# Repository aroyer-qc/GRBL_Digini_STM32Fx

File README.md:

# GRBL_Digini_STM32Fx

Grbl is a no-compromise, high performance, low cost alternative to parallel-port-based motion control for CNC milling. This version will run on a stm32f7-discovery and later on other STM32 family.
The controller is written in highly optimized C utilizing every clever feature of the STM32F7 to achieve precise timing and asynchronous operation. It will be able to maintain more than the original 30kHz from Arduino of stable, jitter free control pulses.

Digini is a HAL and GUI library written in embedded C++. It is highly optimized and is also a highly configurable graphic library. GUI is based on Widget/Service concept. What this mean is, the application like GRBL run on his own loop, and is not aware the GUI even exist. the GUI on his side is running multiple task to display graphic page. Those page are a chain list of widget, and those widget are configured with information about position, graphic to use, service to call to display the proper information and link to other page. all information is processed via variables and/or call to users functions.

  ## Note(s):
  
>   * GRBL is a great application for me to develop the graphic DIGINI platform.
>   * Widget are easy to add in Digini.
    
  ## Feature:

>   * Code is C++ (following embedded rules found on IAR C++ document Inefficiencies of C++: Fact or Fiction?).
>   * Run on nOS from Jim Tremblay. See [RTOS for microcontrollers](https://github.com/jimtremblay/nOS)
>   * Digini graphics run parallel and independant of the main application, all graphics are handles via service.
>   * Data are display by hooking to variables and/or by calling function(s), input are also done via variables and/or function(s). no graphic code exist in application.
>   * Control over the application can be done via state machine and/or message at the discretion of the application user.
>   * Skin data is loaded from SD card via a skin file (.skn). to build a skin file you can used my application [GUI_Builder](https://github.com/aroyer-qc/GUI_Builder)

  ## Widget list so far:
  
>    * Background widget to display background layer.
>    * Basic box.
>    * Basic button with text (no graphic).
>    * Basic rectangle.
>    * Button with text, icon and support for multiple graphic so button can have different state. ( EX. normal, pressed, gray out)
>    * Exchange is a non grahical special widget to exchange data between graphic page.
>    * Gif to display gif as animation.
>    * Icon support for multiple graphic to display different state.
>    * Label to display static/formatted label. also support for different language.
>    * Label list, like label but with a list different label according to state.
>    * Meter, WIP.
>    * Panel, can add touch zone with graphics under other widget.
>    * Progress bar.
>    * Spectrum analyser display (Use data from application, no processing).
>    * Terminal basic terminal screen.
>    * Virtual is a non grahical special widget to decide whart page to display according to application setting.
>    * Virtual windows (WIP).
  
  ## Standard service provided in library
  
>    * SERV_ID_BACK    Service to copy background to background layer.
>    * SERV_ID_BDEF    Service to handle button used only to jump to other page link. Ex. Setting, Back, Ok, etc...
>    * SERV_ID_DATE    Service to return the date of the system into a formatted string.
>    * SERV_ID_DAYS    Service to return the days of the system into a formatted string.
>    * SERV_ID_INPT    Service to input data via a generic page in decimal or hexa.
>    * SERV_ID_INPS    Service to input string via a generic page. (WIP).
>    * SERV_ID_NONE    Service to return default state
>    * SERV_ID_RFSH    Service to display static widget
>    * SERV_ID_SKLD    Service to return percentage of the skin loading progression
>    * SERV_ID_TIME    Service to return the timeof the system into a formatted string (can handle all format defined by user).
>    * SERV_ID_XCHG    Service to exchange data via structure between page. (title, min, max, value, edit type)

  ## Required Module:
  
>    *   Digini                        (Branch Develop)
>    *   module_FatFs                  (Branch main)
>    *   module_jpg                    (Branch main)
>    *   lwip                          (Branch STABLE_2_1_x)
>    *   module_picopng                (Branch main)
>    *   module_STM32F7xx              (Branch main)
>    *   nOS                           (Branch master)

  ## Known issues
  
>    * Stepper not yet working, I need to test the STM32 timer and integrate them into the GRBL code.
>    * Spindle not yet working, PWM need to be tested and integrated.
>    * Cross exchange GRBL <-> GUI to be done..
>    * A lot of graphic page to fix/complete.
>    * Add sound capability to get some aptic feedback.

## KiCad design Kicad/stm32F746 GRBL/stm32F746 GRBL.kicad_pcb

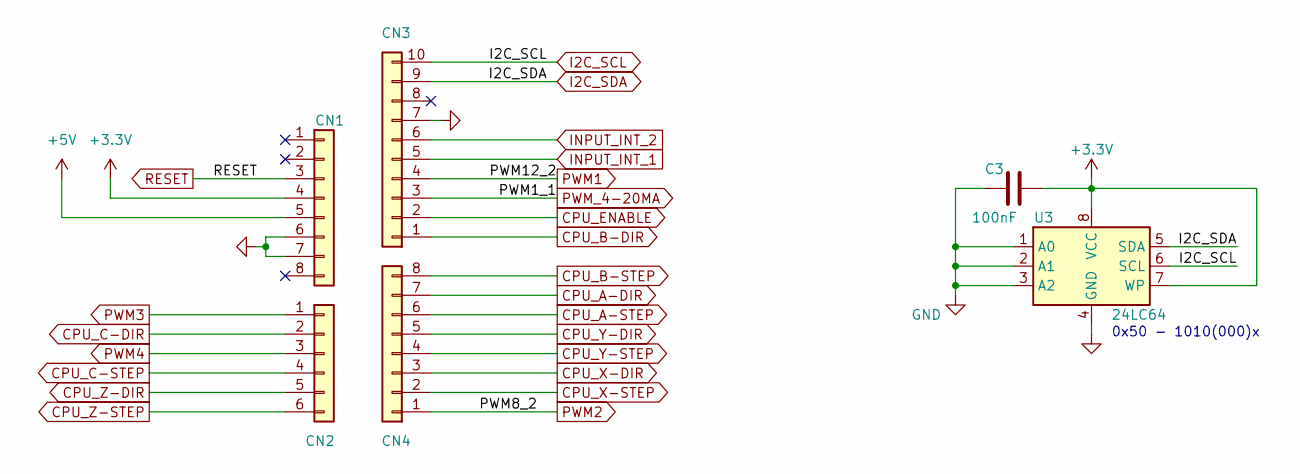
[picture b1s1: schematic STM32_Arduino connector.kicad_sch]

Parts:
C3: 100nF; C_0805_2012Metric
CN1, CN4: PinHeader_1x08_P2.54mm_Vertical
CN2: PinHeader_1x06_P2.54mm_Vertical
CN3: PinHeader_1x10_P2.54mm_Vertical
U3: 24LC64; SOIC-8_3.9x4.9mm_P1.27mm

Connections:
+3.3V: C3.2, CN1.4, U3.7 (WP), U3.8 (VCC)
+5V: CN1.5
CPU_A-DIR: CN4.7; also elsewhere on the board
CPU_A-STEP: CN4.6; also elsewhere on the board
CPU_B-DIR: CN3.1; also elsewhere on the board
CPU_B-STEP: CN4.8; also elsewhere on the board
CPU_C-DIR: CN2.2; also elsewhere on the board
CPU_C-STEP: CN2.4; also elsewhere on the board
CPU_ENABLE: CN3.2; also elsewhere on the board
CPU_X-DIR: CN4.3; also elsewhere on the board
CPU_X-STEP: CN4.2; also elsewhere on the board
CPU_Y-DIR: CN4.5; also elsewhere on the board
CPU_Y-STEP: CN4.4; also elsewhere on the board
CPU_Z-DIR: CN2.5; also elsewhere on the board
CPU_Z-STEP: CN2.6; also elsewhere on the board
GND: C3.1, CN1.6, CN1.7, CN3.7, U3.1 (A0), U3.2 (A1), U3.3 (A2), U3.4 (GND); also elsewhere on the board
I2C_SCL: CN3.10, U3.6 (SCL); also elsewhere on the board
I2C_SDA: CN3.9, U3.5 (SDA); also elsewhere on the board
INPUT_INT_1: CN3.5; also elsewhere on the board
INPUT_INT_2: CN3.6; also elsewhere on the board
PWM1: CN3.4; also elsewhere on the board
PWM2: CN4.1; also elsewhere on the board
PWM3: CN2.1; also elsewhere on the board
PWM4: CN2.3; also elsewhere on the board
PWM_4-20MA: CN3.3; also elsewhere on the board
RESET: CN1.3; also elsewhere on the board

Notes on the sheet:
0x50 - 1010(000)x

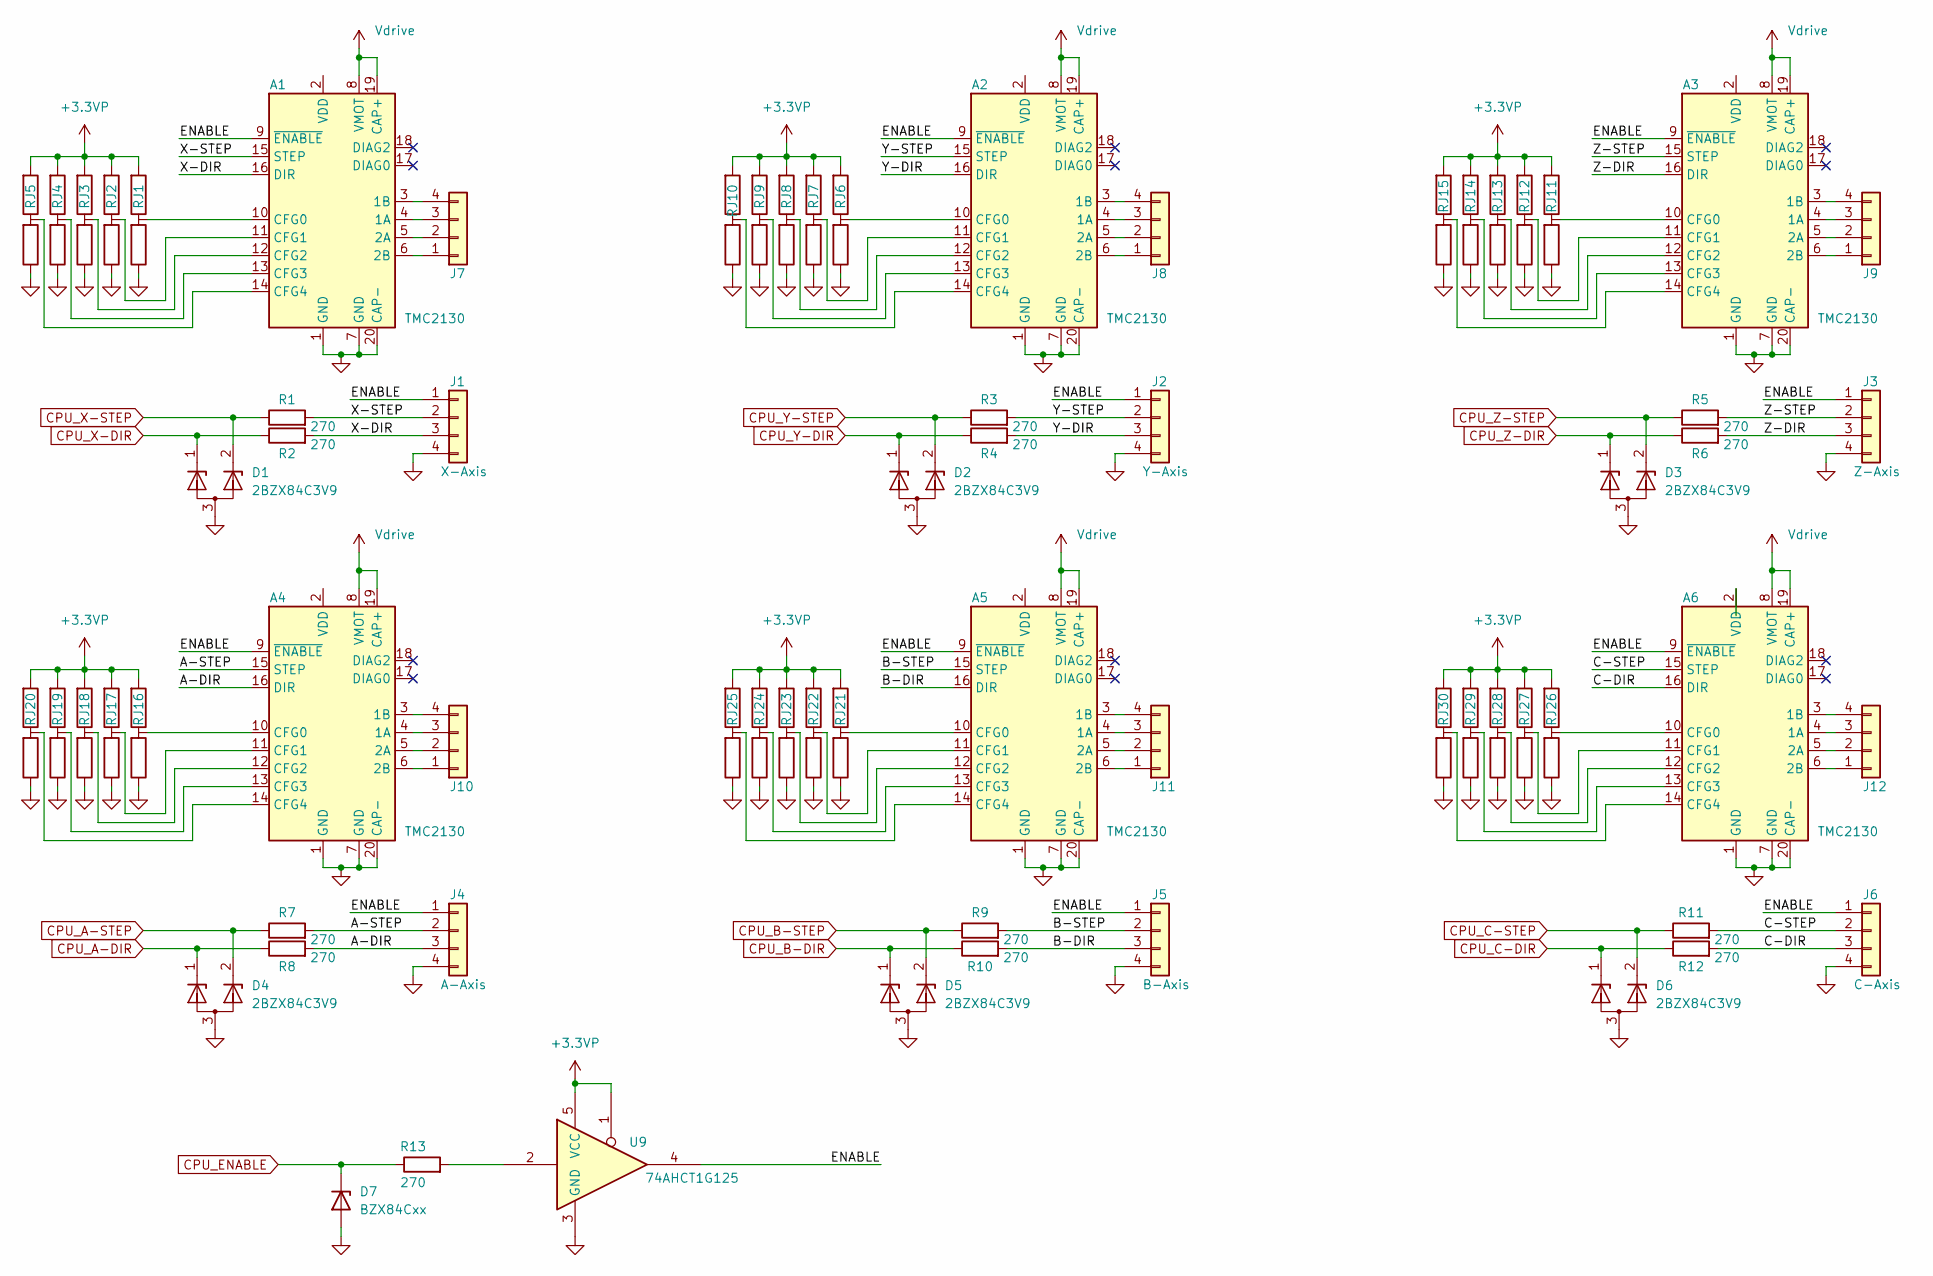
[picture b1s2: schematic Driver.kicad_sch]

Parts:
A1, A2, A3, A4, A5, A6: TMC2130_Breakout_TMC2130; TMC2130_Breakout-16_15.2x20.3mm
D1, D2, D3, D4, D5, D6: 2BZX84C3V9; SOT-23
D7: BZX84Cxx; SOT-23
J1: X-Axis; JST_XH_B4B-XH-A_1x04_P2.50mm_Vertical
J2: Y-Axis; JST_XH_B4B-XH-A_1x04_P2.50mm_Vertical
J3: Z-Axis; JST_XH_B4B-XH-A_1x04_P2.50mm_Vertical
J4: A-Axis; JST_XH_B4B-XH-A_1x04_P2.50mm_Vertical
J5: B-Axis; JST_XH_B4B-XH-A_1x04_P2.50mm_Vertical
J6: C-Axis; JST_XH_B4B-XH-A_1x04_P2.50mm_Vertical
J7, J8, J9, J10, J11, J12: Conn_01x04; JST_XH_B4B-XH-A_1x04_P2.50mm_Vertical
R1, R2, R3, R4, R5, R6, R7, R8, R9, R10, R11, R12, R13: 270; R_0805_2012Metric
RJ1, RJ2, RJ3, RJ4, RJ5, RJ6, RJ7, RJ8, RJ9, RJ10, RJ11, RJ12, RJ13, RJ14, RJ15, RJ16, RJ17, RJ18, RJ19, RJ20, RJ21, RJ22, RJ23, RJ24, RJ25, RJ26, RJ27, RJ28, RJ29, RJ30: 0R; RJ_3 pads_0805_2012Metric
U9: 74AHCT1G125; SOT-353_SC-70-5

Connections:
+3.3VP: RJ1.1, RJ2.1, RJ3.1, RJ4.1, RJ5.1, RJ6.1, RJ7.1, RJ8.1, RJ9.1, RJ10.1, RJ11.1, RJ12.1, RJ13.1, RJ14.1, RJ15.1, RJ16.1, RJ17.1, RJ18.1, RJ19.1, RJ20.1, RJ21.1, RJ22.1, RJ23.1, RJ24.1, RJ25.1, RJ26.1, RJ27.1, RJ28.1, RJ29.1, RJ30.1, U9.1, U9.5 (VCC); also elsewhere on the board
/Driver/A-DIR: A4.16 (DIR), J4.3, R8.2
/Driver/A-STEP: A4.15 (STEP), J4.2, R7.2
/Driver/B-DIR: A5.16 (DIR), J5.3, R10.2
/Driver/B-STEP: A5.15 (STEP), J5.2, R9.2
/Driver/C-DIR: A6.16 (DIR), J6.3, R12.2
/Driver/C-STEP: A6.15 (STEP), J6.2, R11.2
/Driver/ENABLE: A1.9 (~ENABLE), A2.9 (~ENABLE), A3.9 (~ENABLE), A4.9 (~ENABLE), A5.9 (~ENABLE), A6.9 (~ENABLE), J1.1, J2.1, J3.1, J4.1, J5.1, J6.1, U9.4
/Driver/X-DIR: A1.16 (DIR), J1.3, R2.2
/Driver/X-STEP: A1.15 (STEP), J1.2, R1.2
/Driver/Y-DIR: A2.16 (DIR), J2.3, R4.2
/Driver/Y-STEP: A2.15 (STEP), J2.2, R3.2
/Driver/Z-DIR: A3.16 (DIR), J3.3, R6.2
/Driver/Z-STEP: A3.15 (STEP), J3.2, R5.2
CPU_A-DIR: D4.1 (K), R8.1; also elsewhere on the board
CPU_A-STEP: D4.2 (K), R7.1; also elsewhere on the board
CPU_B-DIR: D5.1 (K), R10.1; also elsewhere on the board
CPU_B-STEP: D5.2 (K), R9.1; also elsewhere on the board
CPU_C-DIR: D6.1 (K), R12.1; also elsewhere on the board
CPU_C-STEP: D6.2 (K), R11.1; also elsewhere on the board
CPU_ENABLE: D7.3 (K), R13.1; also elsewhere on the board
CPU_X-DIR: D1.1 (K), R2.1; also elsewhere on the board
CPU_X-STEP: D1.2 (K), R1.1; also elsewhere on the board
CPU_Y-DIR: D2.1 (K), R4.1; also elsewhere on the board
CPU_Y-STEP: D2.2 (K), R3.1; also elsewhere on the board
CPU_Z-DIR: D3.1 (K), R6.1; also elsewhere on the board
CPU_Z-STEP: D3.2 (K), R5.1; also elsewhere on the board
GND: A1.1 (GND), A1.7 (GND), A1.20 (CAP-), A2.1 (GND), A2.7 (GND), A2.20 (CAP-), A3.1 (GND), A3.7 (GND), A3.20 (CAP-), A4.1 (GND), A4.7 (GND), A4.20 (CAP-), A5.1 (GND), A5.7 (GND), A5.20 (CAP-), A6.1 (GND), A6.7 (GND), A6.20 (CAP-), D1.3 (A), D2.3 (A), D3.3 (A), D4.3 (A), D5.3 (A), D6.3 (A), D7.1 (A), J1.4, J2.4, J3.4, J4.4, J5.4, J6.4, RJ1.3, RJ2.3, RJ3.3, RJ4.3, RJ5.3, RJ6.3, RJ7.3, RJ8.3, RJ9.3, RJ10.3, RJ11.3, RJ12.3, RJ13.3, RJ14.3, RJ15.3, RJ16.3, RJ17.3, RJ18.3, RJ19.3, RJ20.3, RJ21.3, RJ22.3, RJ23.3, RJ24.3, RJ25.3, RJ26.3, RJ27.3, RJ28.3, RJ29.3, RJ30.3, U9.3 (GND); also elsewhere on the board
unnamed: A1.4 (1A), J7.3
unnamed: A1.3 (1B), J7.4
unnamed: A1.5 (2A), J7.2
unnamed: A1.6 (2B), J7.1
unnamed: A1.10 (CFG0), RJ1.2
unnamed: A1.11 (CFG1), RJ2.2
unnamed: A1.12 (CFG2), RJ3.2
unnamed: A1.13 (CFG3), RJ4.2
unnamed: A1.14 (CFG4), RJ5.2
unnamed: A2.4 (1A), J8.3
unnamed: A2.3 (1B), J8.4
unnamed: A2.5 (2A), J8.2
unnamed: A2.6 (2B), J8.1
unnamed: A2.10 (CFG0), RJ6.2
unnamed: A2.11 (CFG1), RJ7.2
unnamed: A2.12 (CFG2), RJ8.2
unnamed: A2.13 (CFG3), RJ9.2
unnamed: A2.14 (CFG4), RJ10.2
unnamed: A3.4 (1A), J9.3
unnamed: A3.3 (1B), J9.4
unnamed: A3.5 (2A), J9.2
unnamed: A3.6 (2B), J9.1
unnamed: A3.10 (CFG0), RJ11.2
unnamed: A3.11 (CFG1), RJ12.2
unnamed: A3.12 (CFG2), RJ13.2
unnamed: A3.13 (CFG3), RJ14.2
unnamed: A3.14 (CFG4), RJ15.2
unnamed: A4.4 (1A), J10.3
unnamed: A4.3 (1B), J10.4
unnamed: A4.5 (2A), J10.2
unnamed: A4.6 (2B), J10.1
unnamed: A4.10 (CFG0), RJ16.2
unnamed: A4.11 (CFG1), RJ17.2
unnamed: A4.12 (CFG2), RJ18.2
unnamed: A4.13 (CFG3), RJ19.2
unnamed: A4.14 (CFG4), RJ20.2
unnamed: A5.4 (1A), J11.3
unnamed: A5.3 (1B), J11.4
unnamed: A5.5 (2A), J11.2
unnamed: A5.6 (2B), J11.1
unnamed: A5.10 (CFG0), RJ21.2
unnamed: A5.11 (CFG1), RJ22.2
unnamed: A5.12 (CFG2), RJ23.2
unnamed: A5.13 (CFG3), RJ24.2
unnamed: A5.14 (CFG4), RJ25.2
unnamed: A6.4 (1A), J12.3
unnamed: A6.3 (1B), J12.4
unnamed: A6.5 (2A), J12.2
unnamed: A6.6 (2B), J12.1
unnamed: A6.10 (CFG0), RJ26.2
unnamed: A6.11 (CFG1), RJ27.2
unnamed: A6.12 (CFG2), RJ28.2
unnamed: A6.13 (CFG3), RJ29.2
unnamed: A6.14 (CFG4), RJ30.2
unnamed: R13.2, U9.2
Vdrive: A1.8 (VMOT), A1.19 (CAP+), A2.8 (VMOT), A2.19 (CAP+), A3.8 (VMOT), A3.19 (CAP+), A4.8 (VMOT), A4.19 (CAP+), A5.8 (VMOT), A5.19 (CAP+), A6.8 (VMOT), A6.19 (CAP+); also elsewhere on the board

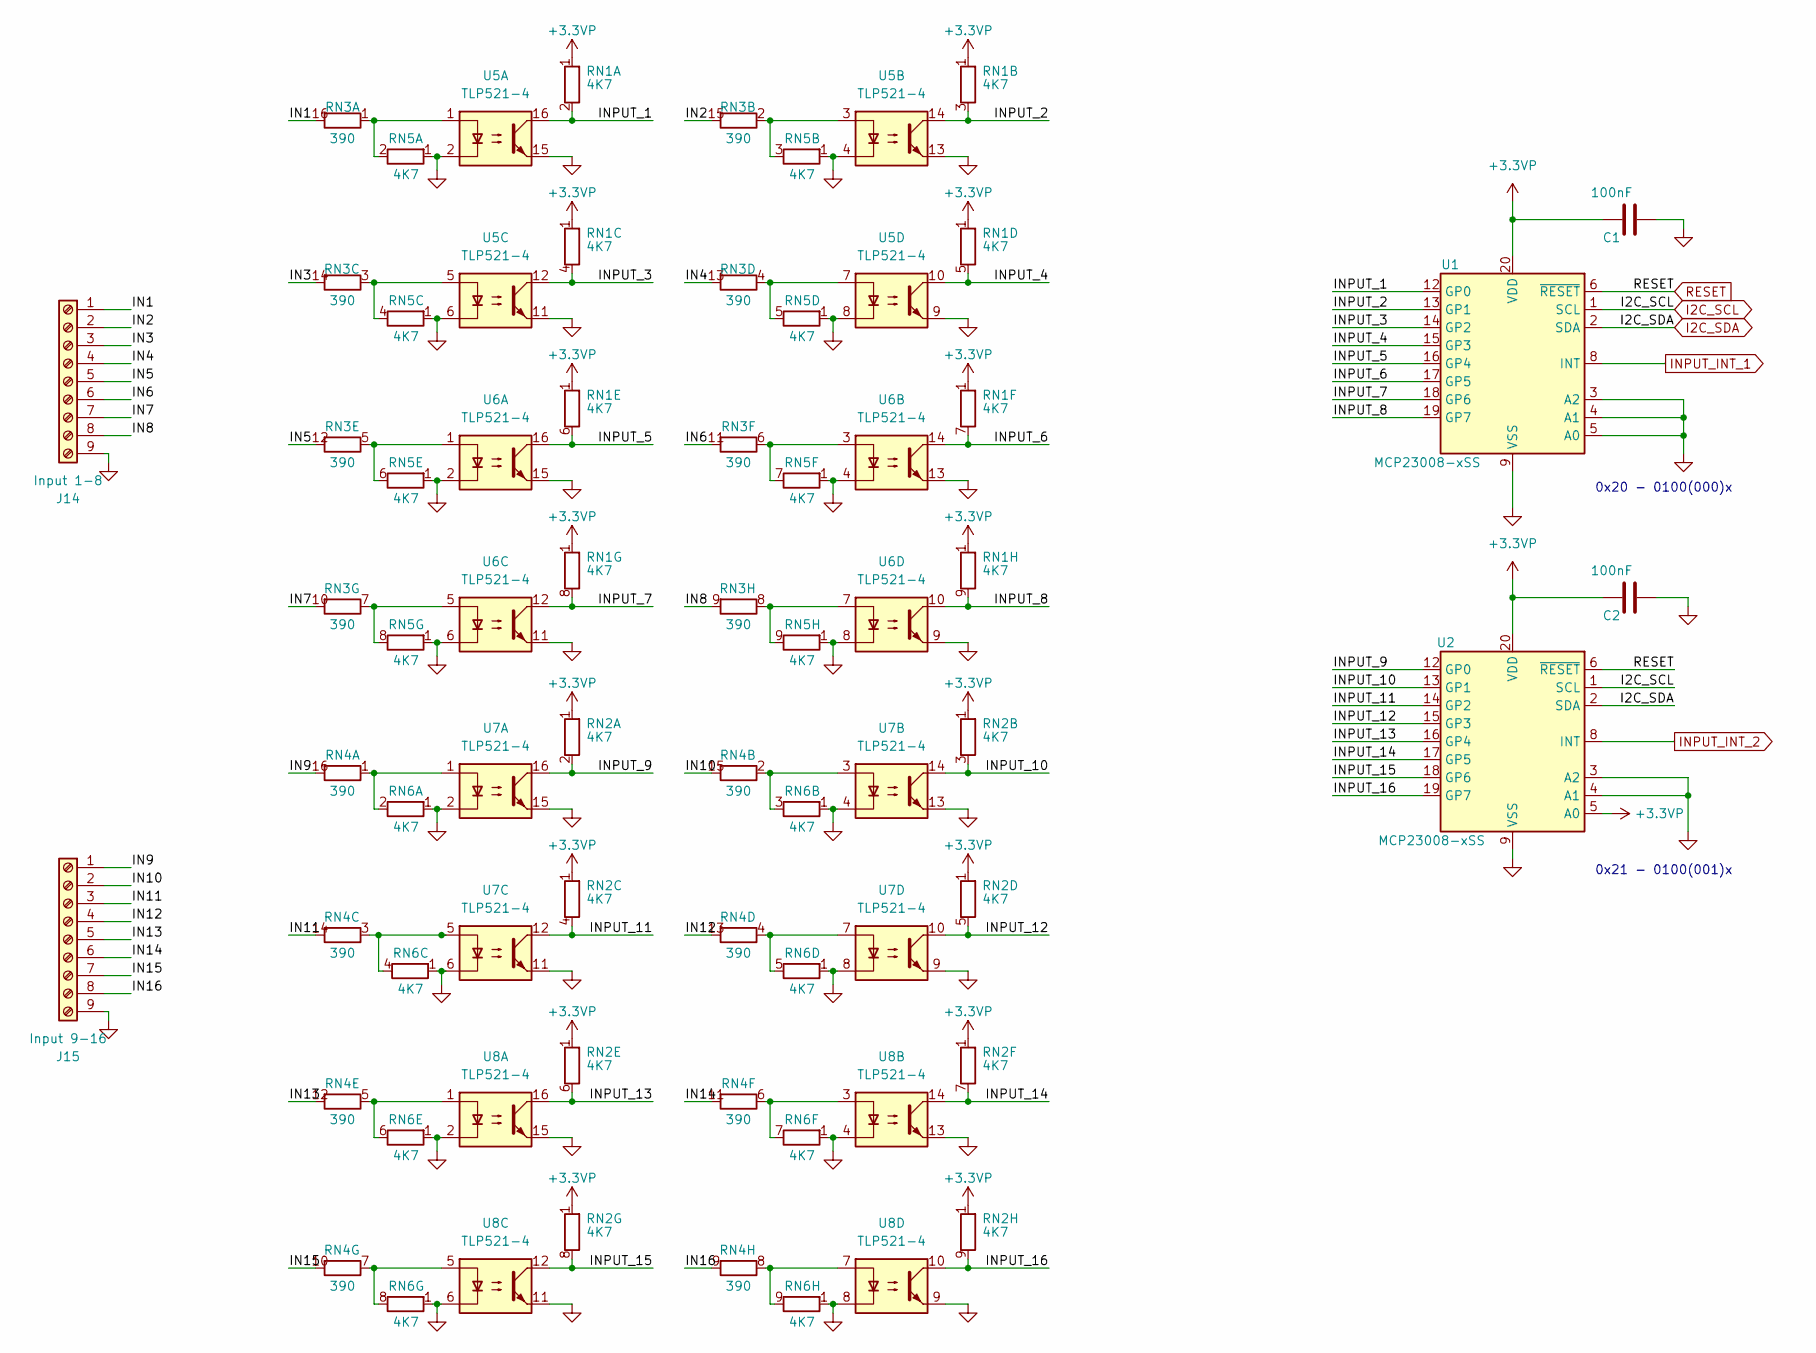
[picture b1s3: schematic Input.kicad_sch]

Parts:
C1, C2: 100nF; C_0805_2012Metric
J14: Input 1-8; TerminalBlock_TE_282834-9_1x09_P2.54mm_Horizontal
J15: Input 9-16; TerminalBlock_TE_282834-9_1x09_P2.54mm_Horizontal
RN1, RN2, RN5, RN6: 4K7; R_Array_SIP9
RN3, RN4: 390; SOIC-16_4.55x10.3mm_P1.27mm; Digikey 4816P-1-391LF
U1, U2: MCP23008-xSS; SSOP-20_5.3x7.2mm_P0.65mm
U5, U6, U7, U8: TLP521-4; SOIC-16_4.55x10.3mm_P1.27mm

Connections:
+3.3VP: C1.1, C2.1, RN1.1 (R1), RN2.1 (R1), U1.20 (VDD), U2.5 (A0), U2.20 (VDD); also elsewhere on the board
/Input/IN1: J14.1, RN3.16 (R1.2)
/Input/IN2: J14.2, RN3.15 (R2.2)
/Input/IN3: J14.3, RN3.14 (R3.2)
/Input/IN4: J14.4, RN3.13 (R4.2)
/Input/IN5: J14.5, RN3.12 (R5.2)
/Input/IN6: J14.6, RN3.11 (R6.2)
/Input/IN7: J14.7, RN3.10 (R7.2)
/Input/IN8: J14.8, RN3.9 (R8.2)
/Input/IN9: J15.1, RN4.16 (R1.2)
/Input/IN10: J15.2, RN4.15 (R2.2)
/Input/IN11: J15.3, RN4.14 (R3.2)
/Input/IN12: J15.4, RN4.13 (R4.2)
/Input/IN13: J15.5, RN4.12 (R5.2)
/Input/IN14: J15.6, RN4.11 (R6.2)
/Input/IN15: J15.7, RN4.10 (R7.2)
/Input/IN16: J15.8, RN4.9 (R8.2)
/Input/INPUT_1: RN1.2 (R1.2), U1.12 (GP0), U5.16
/Input/INPUT_2: RN1.3 (R2.2), U1.13 (GP1), U5.14
/Input/INPUT_3: RN1.4 (R3.2), U1.14 (GP2), U5.12
/Input/INPUT_4: RN1.5 (R4.2), U1.15 (GP3), U5.10
/Input/INPUT_5: RN1.6 (R5.2), U1.16 (GP4), U6.16
/Input/INPUT_6: RN1.7 (R6.2), U1.17 (GP5), U6.14
/Input/INPUT_7: RN1.8 (R7.2), U1.18 (GP6), U6.12
/Input/INPUT_8: RN1.9 (R8.2), U1.19 (GP7), U6.10
/Input/INPUT_9: RN2.2 (R1.2), U2.12 (GP0), U7.16
/Input/INPUT_10: RN2.3 (R2.2), U2.13 (GP1), U7.14
/Input/INPUT_11: RN2.4 (R3.2), U2.14 (GP2), U7.12
/Input/INPUT_12: RN2.5 (R4.2), U2.15 (GP3), U7.10
/Input/INPUT_13: RN2.6 (R5.2), U2.16 (GP4), U8.16
/Input/INPUT_14: RN2.7 (R6.2), U2.17 (GP5), U8.14
/Input/INPUT_15: RN2.8 (R7.2), U2.18 (GP6), U8.12
/Input/INPUT_16: RN2.9 (R8.2), U2.19 (GP7), U8.10
GND: C1.2, C2.2, J14.9, J15.9, RN5.1 (R1), RN6.1 (R1), U1.3 (A2), U1.4 (A1), U1.5 (A0), U1.9 (VSS), U2.3 (A2), U2.4 (A1), U2.9 (VSS), U5.2, U5.4, U5.6, U5.8, U5.9, U5.11, U5.13, U5.15, U6.2, U6.4, U6.6, U6.8, U6.9, U6.11, U6.13, U6.15, U7.2, U7.4, U7.6, U7.8, U7.9, U7.11, U7.13, U7.15, U8.2, U8.4, U8.6, U8.8, U8.9, U8.11, U8.13, U8.15; also elsewhere on the board
I2C_SCL: U1.1 (SCL), U2.1 (SCL); also elsewhere on the board
I2C_SDA: U1.2 (SDA), U2.2 (SDA); also elsewhere on the board
INPUT_INT_1: U1.8 (INT); also elsewhere on the board
INPUT_INT_2: U2.8 (INT); also elsewhere on the board
unnamed: RN3.1 (R1.1), RN5.2 (R1.2), U5.1
unnamed: RN3.2 (R2.1), RN5.3 (R2.2), U5.3
unnamed: RN3.3 (R3.1), RN5.4 (R3.2), U5.5
unnamed: RN3.4 (R4.1), RN5.5 (R4.2), U5.7
unnamed: RN3.5 (R5.1), RN5.6 (R5.2), U6.1
unnamed: RN3.6 (R6.1), RN5.7 (R6.2), U6.3
unnamed: RN3.7 (R7.1), RN5.8 (R7.2), U6.5
unnamed: RN3.8 (R8.1), RN5.9 (R8.2), U6.7
unnamed: RN4.1 (R1.1), RN6.2 (R1.2), U7.1
unnamed: RN4.2 (R2.1), RN6.3 (R2.2), U7.3
unnamed: RN4.3 (R3.1), RN6.4 (R3.2), U7.5
unnamed: RN4.4 (R4.1), RN6.5 (R4.2), U7.7
unnamed: RN4.5 (R5.1), RN6.6 (R5.2), U8.1
unnamed: RN4.6 (R6.1), RN6.7 (R6.2), U8.3
unnamed: RN4.7 (R7.1), RN6.8 (R7.2), U8.5
unnamed: RN4.8 (R8.1), RN6.9 (R8.2), U8.7
RESET: U1.6 (~RESET), U2.6 (~RESET); also elsewhere on the board

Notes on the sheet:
0x21 - 0100(001)x
0x20 - 0100(000)x

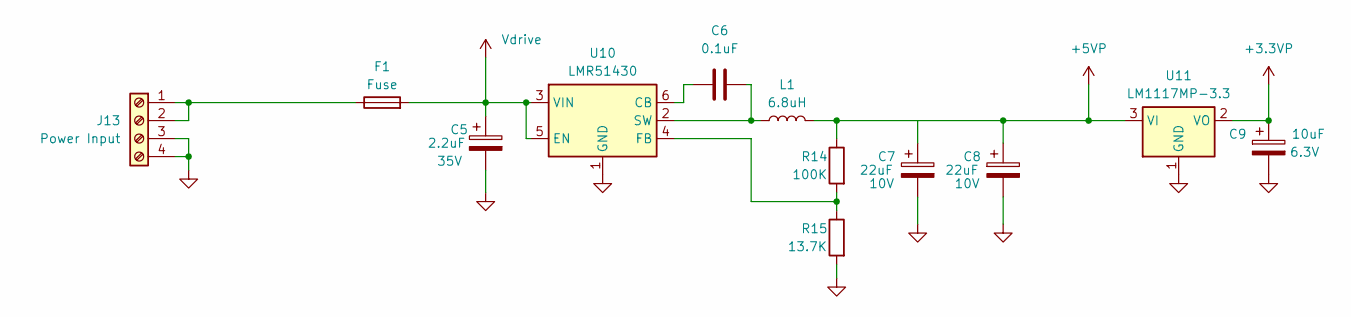
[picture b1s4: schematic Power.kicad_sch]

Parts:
C5: 2.2uF; C_0805_2012Metric_Pad1.18x1.45mm_HandSolder; Voltage 35V; Digikey 445-6963-1-ND
C6: 0.1uF; C_0805_2012Metric
C7, C8: 22uF; C_0805_2012Metric_Pad1.18x1.45mm_HandSolder; Voltage 10V; Digikey 490-10511-1-ND
C9: 10uF; CP_EIA-3528-15_AVX-H_Pad1.50x2.35mm_HandSolder; Voltage 6.3V; Digikey 399-T498B106K006ATE2K1CT-ND
F1: Fuse; Fuseholder_Littelfuse_Nano2_154x; Digikey F1227CT-ND
J13: Power Input; PhoenixContact_MSTBA_2,5_4-G-5,08_1x04_P5.08mm_Horizontal
L1: 6.8uH; L_Bourns_SRP5030T; Digikey SRP5030T-6R8MTR-ND
R14: 100K; R_0805_2012Metric_Pad1.20x1.40mm_HandSolder
R15: 13.7K; R_0805_2012Metric_Pad1.20x1.40mm_HandSolder
U10: LMR51430; SOT-23-6
U11: LM1117MP-3.3; SOT-223-3_TabPin2

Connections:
+3.3VP: C9.1, U11.2 (VO); also elsewhere on the board
+5VP: C8.1, L1.2, R14.1, U11.3 (VI); also elsewhere on the board
GND: C5.2, C7.2, C8.2, C9.2, J13.3, J13.4, R15.2, U10.1 (GND), U11.1 (GND); also elsewhere on the board
unnamed: F1.1, J13.1, J13.2
unnamed: C6.1, U10.6 (CB)
unnamed: R14.2, R15.1, U10.4 (FB)
unnamed: C6.2, L1.1, U10.2 (SW)
Vdrive: C5.1, F1.2, U10.3 (VIN), U10.5 (EN); also elsewhere on the board

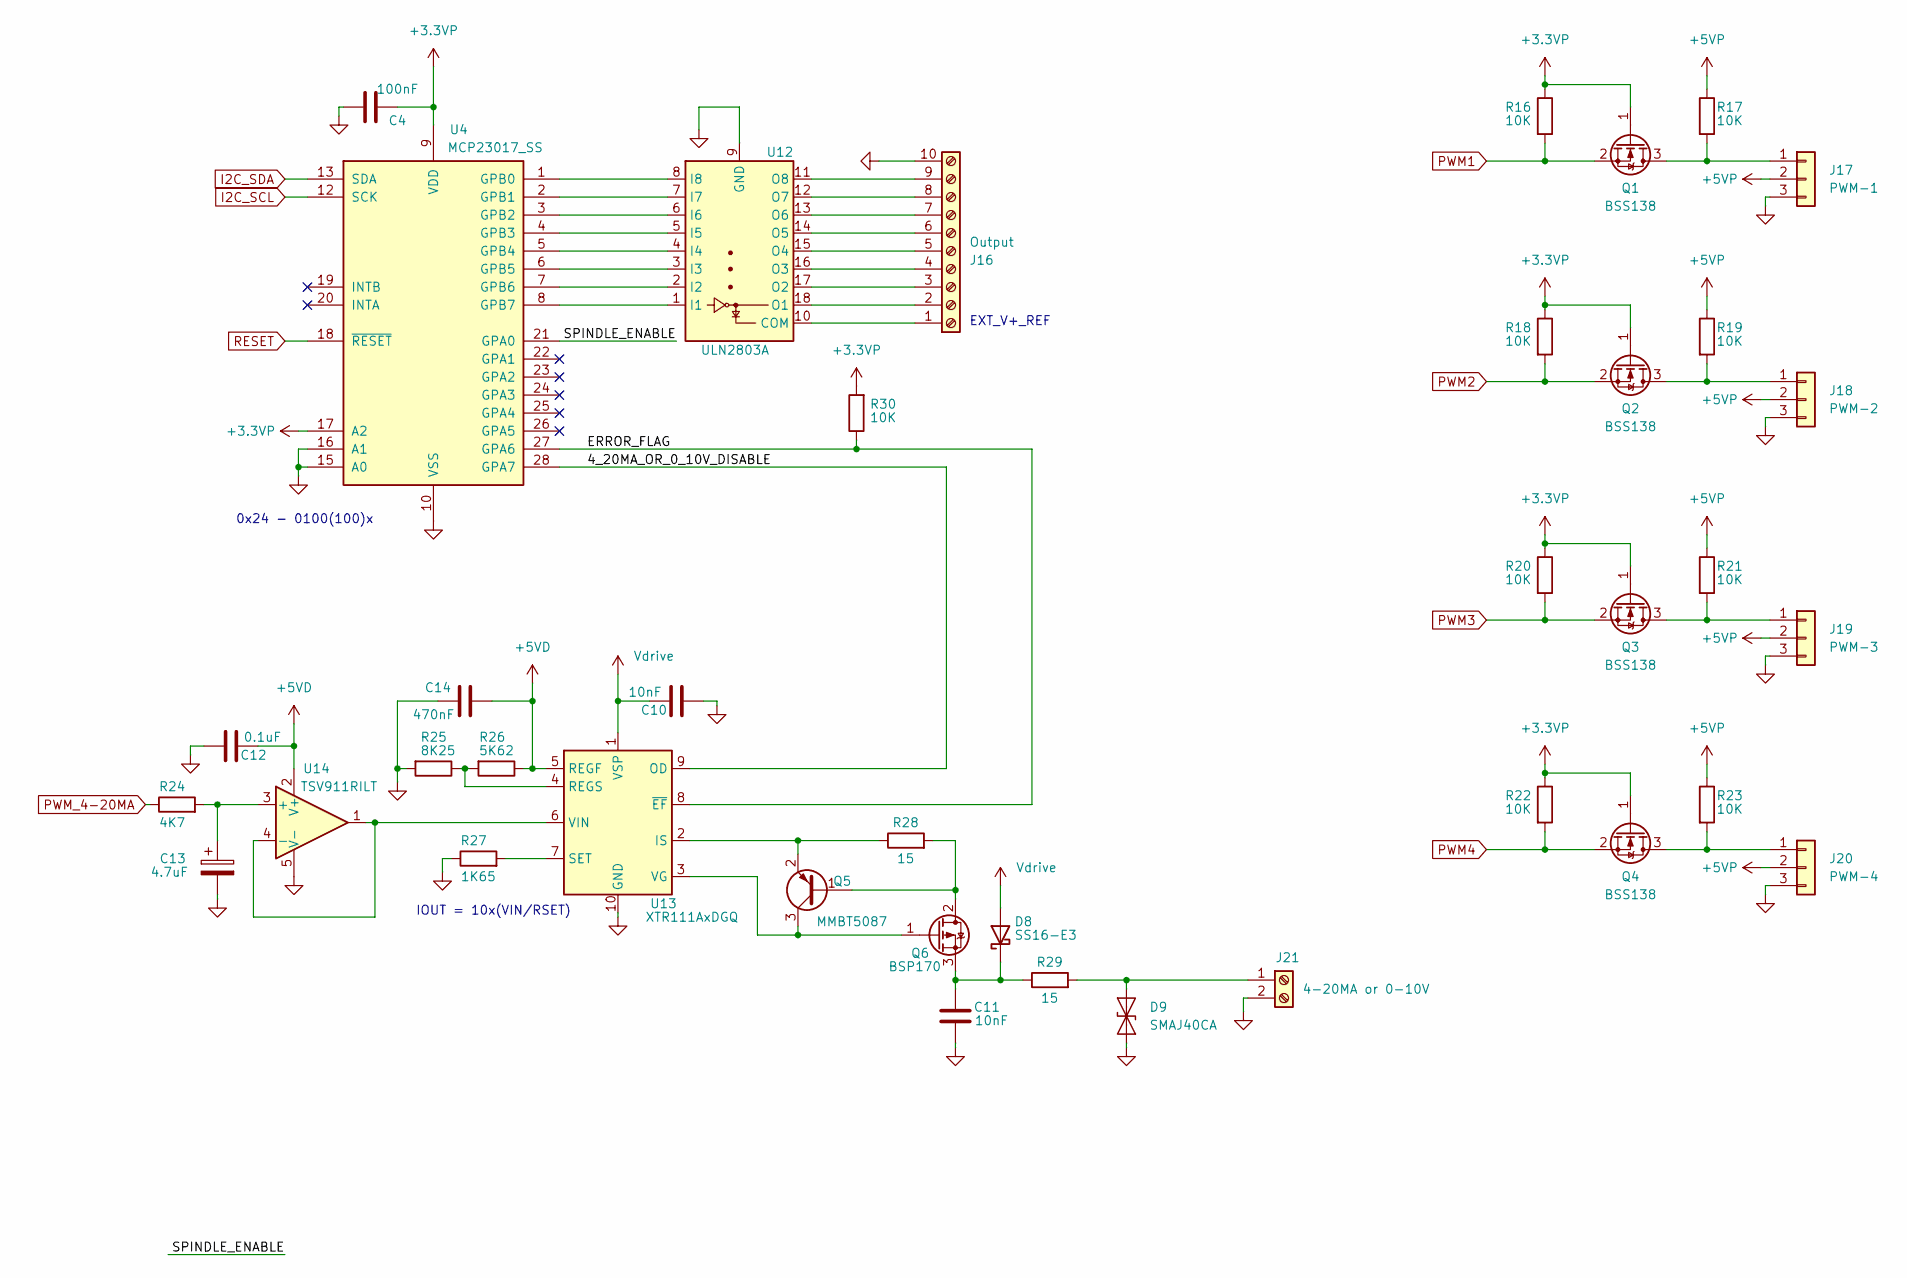
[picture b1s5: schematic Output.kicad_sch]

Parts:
C4: 100nF; C_0805_2012Metric
C10, C11: 10nF; C_0805_2012Metric
C12: 0.1uF; C_0805_2012Metric
C13: 4.7uF; C_0805_2012Metric
C14: 470nF; C_0805_2012Metric
D8: SS16-E3; D_SMA; Digikey SS16-E3/61TGICT-ND
D9: SMAJ40CA; D_SMA
J16: Output; TerminalBlock_TE_1-282834-0_1x10_P2.54mm_Horizontal
J17: PWM-1; PinHeader_1x03_P2.54mm_Vertical
J18: PWM-2; PinHeader_1x03_P2.54mm_Vertical
J19: PWM-3; PinHeader_1x03_P2.54mm_Vertical
J20: PWM-4; PinHeader_1x03_P2.54mm_Vertical
J21: 4-20MA or 0-10V; TerminalBlock_TE_282834-2_1x02_P2.54mm_Horizontal
Q1, Q2, Q3, Q4: BSS138; SOT-23
Q5: MMBT5087; SOT-23
Q6: BSP170; SOT-223-3_TabPin2; Digikey BSP170PL6327INCT-ND
R16, R17, R18, R19, R20, R21, R22, R23, R30: 10K; R_0805_2012Metric_Pad1.20x1.40mm_HandSolder
R24: 4K7; R_0805_2012Metric_Pad1.20x1.40mm_HandSolder
R25: 8K25; R_0805_2012Metric_Pad1.20x1.40mm_HandSolder
R26: 5K62; R_0805_2012Metric_Pad1.20x1.40mm_HandSolder
R27: 1K65; R_0805_2012Metric_Pad1.20x1.40mm_HandSolder
R28, R29: 15; R_0805_2012Metric_Pad1.20x1.40mm_HandSolder
U4: MCP23017_SS; SSOP-28_5.3x10.2mm_P0.65mm
U12: ULN2803A; SOIC-18W_7.5x11.6mm_P1.27mm
U13: XTR111AxDGQ; MSOP-10-1EP_3x3mm_P0.5mm_EP2.2x3.1mm_Mask1.83x1.89mm_Therma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
U14: TSV911RILT; SOT-23-5

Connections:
+3.3VP: C4.1, Q1.1 (G), Q2.1 (G), Q3.1 (G), Q4.1 (G), R16.1, R18.1, R20.1, R22.1, R30.2, U4.9 (VDD), U4.17 (A2); also elsewhere on the board
+5VD: C12.1, C14.2, R26.1, U13.5 (REGF), U14.2 (V+)
+5VP: J17.2, J18.2, J19.2, J20.2, R17.1, R19.1, R21.1, R23.1; also elsewhere on the board
/Output/4_20MA_OR_0_10V_DISABLE: U4.28 (GPA7), U13.9 (OD)
/Output/ERROR_FLAG: R30.1, U4.27 (GPA6), U13.8 (~EF)
/Output/SPINDLE_ENABLE: U4.21 (GPA0)
GND: C4.2, C10.2, C11.2, C12.2, C13.2, C14.1, D9.1 (A1), J16.10, J17.3, J18.3, J19.3, J20.3, J21.2, R25.2, R27.1, U4.10 (VSS), U4.15 (A0), U4.16 (A1), U12.9 (GND), U13.10 (GND), U13.11 (GND), U14.5 (V-); also elsewhere on the board
I2C_SCL: U4.12 (SCK); also elsewhere on the board
I2C_SDA: U4.13 (SDA); also elsewhere on the board
unnamed: C11.1, D8.1 (K), Q6.3 (S), R29.1
unnamed: D9.2 (A2), J21.1, R29.2
unnamed: J16.1, U12.10 (COM)
unnamed: J16.2, U12.18 (O1)
unnamed: J16.3, U12.17 (O2)
unnamed: J16.4, U12.16 (O3)
unnamed: J16.5, U12.15 (O4)
unnamed: J16.6, U12.14 (O5)
unnamed: J16.7, U12.13 (O6)
unnamed: J16.8, U12.12 (O7)
unnamed: J16.9, U12.11 (O8)
unnamed: J17.1, Q1.3 (D), R17.2
unnamed: J18.1, Q2.3 (D), R19.2
unnamed: J19.1, Q3.3 (D), R21.2
unnamed: J20.1, Q4.3 (D), R23.2
unnamed: Q5.1 (B), Q6.2 (D), R28.2
unnamed: Q5.3 (C), Q6.1 (G), U13.3 (VG)
unnamed: Q5.2 (E), R28.1, U13.2 (IS)
unnamed: U4.8 (GPB7), U12.1 (I1)
unnamed: U4.7 (GPB6), U12.2 (I2)
unnamed: U4.6 (GPB5), U12.3 (I3)
unnamed: U4.5 (GPB4), U12.4 (I4)
unnamed: U4.4 (GPB3), U12.5 (I5)
unnamed: U4.3 (GPB2), U12.6 (I6)
unnamed: U4.2 (GPB1), U12.7 (I7)
unnamed: U4.1 (GPB0), U12.8 (I8)
unnamed: R25.1, R26.2, U13.4 (REGS)
unnamed: R27.2, U13.7 (SET)
unnamed: U13.6 (VIN), U14.1, U14.4 (-)
unnamed: C13.1, R24.2, U14.3 (+)
PWM1: Q1.2 (S), R16.2; also elsewhere on the board
PWM2: Q2.2 (S), R18.2; also elsewhere on the board
PWM3: Q3.2 (S), R20.2; also elsewhere on the board
PWM4: Q4.2 (S), R22.2; also elsewhere on the board
PWM_4-20MA: R24.1; also elsewhere on the board
RESET: U4.18 (~RESET); also elsewhere on the board
Vdrive: C10.1, D8.2 (A), U13.1 (VSP); also elsewhere on the board

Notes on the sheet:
0x24 - 0100(100)x
IOUT = 10x(VIN/RSET)
EXT_V+_REF

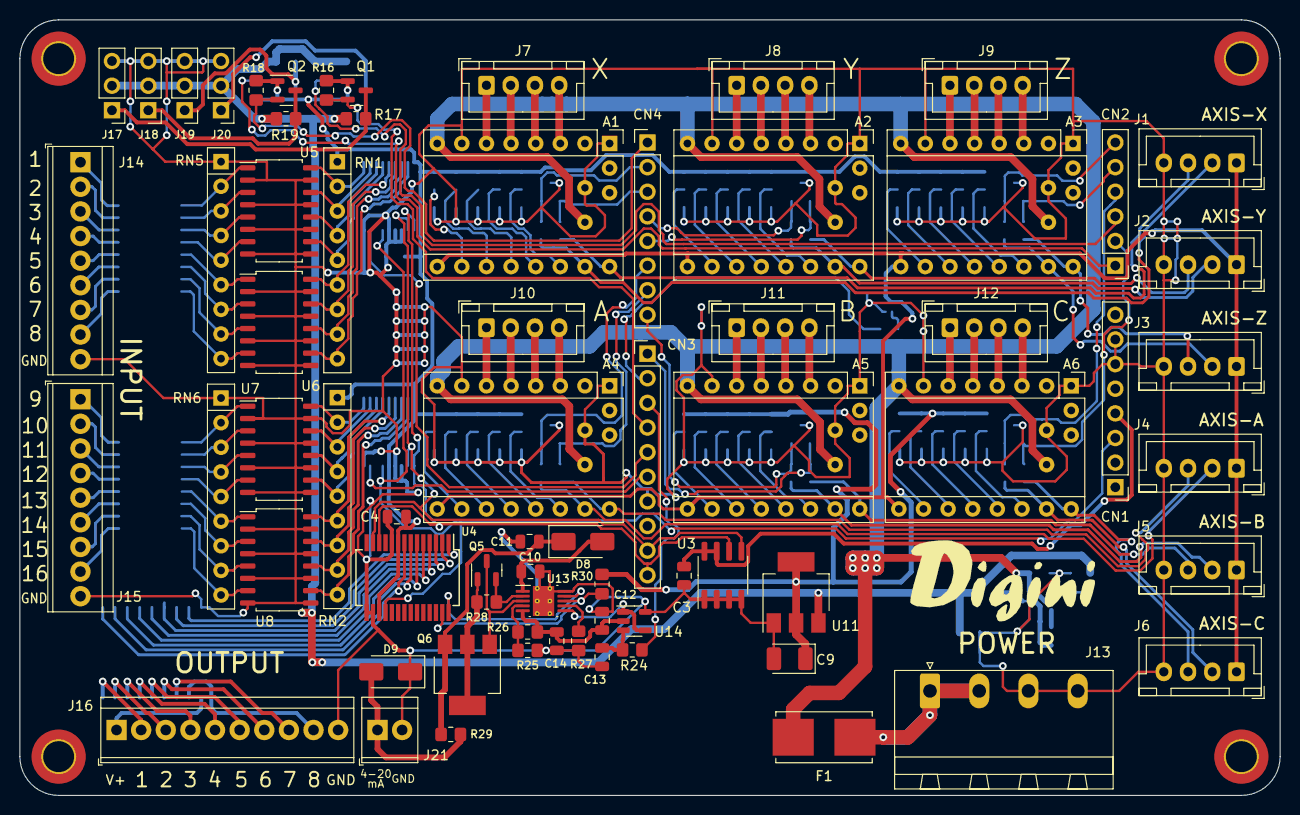
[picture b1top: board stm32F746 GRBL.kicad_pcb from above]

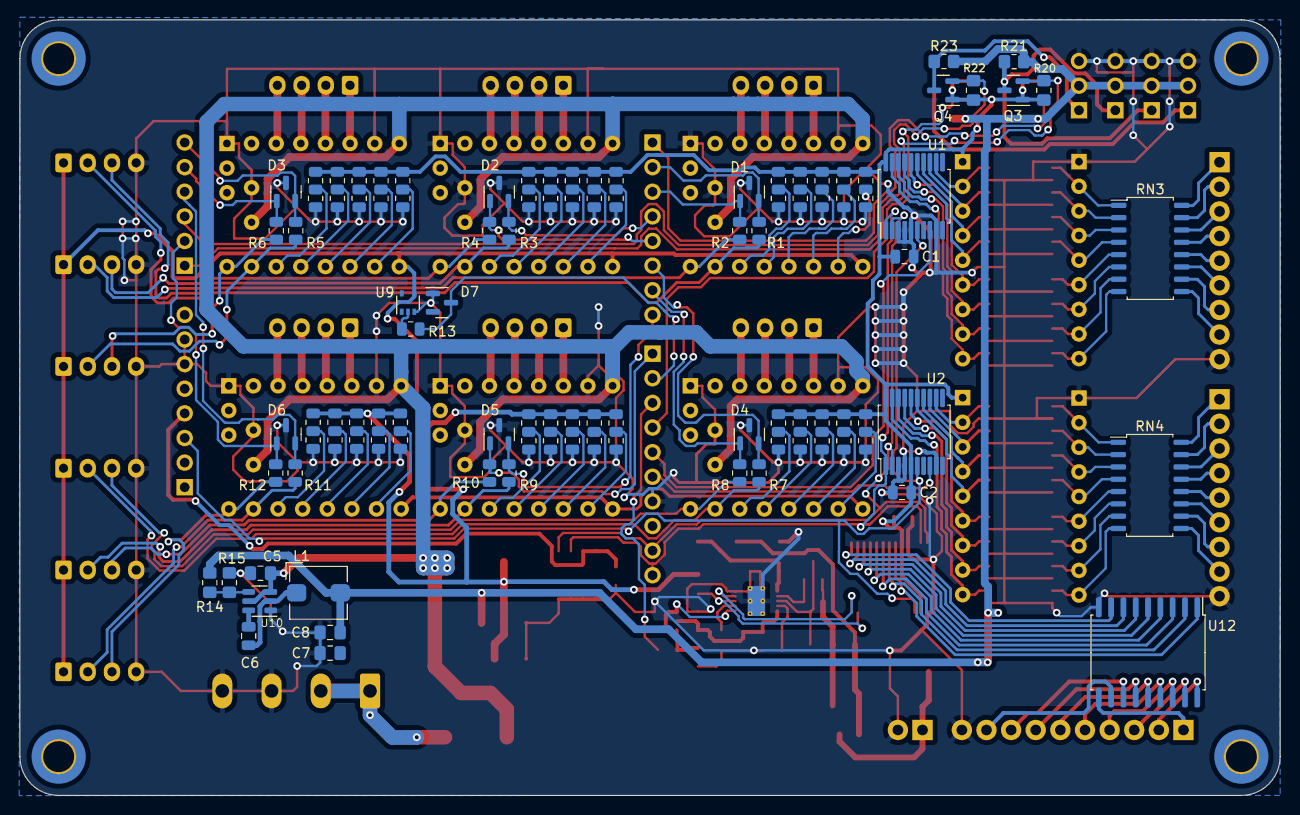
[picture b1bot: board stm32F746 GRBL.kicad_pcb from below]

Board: 2 copper layers, 130.0 x 80.0 mm, 142 parts (72 on the bottom side), 181 nets.

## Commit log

2020-11-18 added grbl logo
2020-11-18 Update LICENSE
2021-01-06 added file to project
2021-01-07 Fix hard fault, improve Edit page, returned value for XCHG are wrong
2021-01-07 added more missing file
2021-01-08 Fix TAB -> 4 spaces
2021-01-08 More Tab Fix
2021-02-12 Sliding WIP
2021-02-12 Sliding page done with complete slide and overlap mode
2021-02-18 Cleanup in digini. prepare to create module
2021-04-30 update logo
2021-04-30 added file to ignore list
2021-08-13 move enum to proper lib location
2021-11-16 adding graph
2021-11-16 restore a missing file
2021-11-22 restore missing file, added graph
2021-11-26 remove module from repo
2021-11-26 add to ignore list
2021-12-14 Code refactoring to match Digini refactoring
2021-12-29 now running, but instable (digini?)
2021-12-30 convert database x-macro to expand
2021-12-31 minor typo
2023-04-24 Adding missing file
2023-04-24 Syncing with other project for STM32F4
2023-04-25 WIP integrate new digini
2023-04-27 clean-up clock_cfg
2023-05-01 rework config file
2023-05-01 SYNC
2023-05-01 SYNC2
2023-05-01 almost compile!!
2023-05-01 closer
2023-05-02 backup
2023-05-08 Project compile, now need to make this all thing work
2023-05-09 added missing util_cfg.h file
2023-05-10 Sync struct naming for LWIP
2023-05-15 Added LWIP in a project
2023-05-16 adding config and ethernet
2023-05-17 WIP CRC
2023-05-18 added CRC method
2023-05-23 adding more functionality and debugging Digini at the same time
2023-05-23 fix taskCOMM
2023-05-25 misc
2023-05-25 check malloc mallinfo to try catching error for allocation memory
2023-05-26 update data usage of stack
2023-05-29 wip LIB_Stacktistic
2023-05-30 WIP Move to MemoryPool
2023-05-30 wip FAT on SDIO.. not working anymore
2023-05-31 wip FatFS SDIO
2023-05-31 Fix I2C, Fix FatFS
2023-06-01 wip fixing GRAFX
2023-06-02 fix label pointer database function
2023-06-07 wip ethernet
2023-06-09 wip ethernet and clean-up
2023-06-15 clean-up and remove support for Flow control in UART
2023-06-15 wip cli
2023-06-16 rework console cli and VT100
2023-06-19 wip vt100
2023-06-21 WIP ETH
2023-06-22 wip vt100_cfg.h
2023-06-26 remove unused file
2023-06-29 wip compile
2023-07-04 major rework on label
2023-07-05 typo
2023-07-06 Adding stack usage
2023-07-13 added PID lib
2023-07-13 remove bunch of file as E2 is move to digini
2023-07-14 WIP E2 and remove unused parameter in Database
2023-07-17 rename some variables
2023-07-18 cleaning GRBL
2023-07-19 wip GRBL remove all config, so all code is there, and can be configured
2023-07-20 Remove #if #endif for most of the config.h
2023-07-25 wip adding DAC
2023-07-26 More DAC, Added DMA Mapping
2023-08-18 adding DS_Digital font to resource
2023-08-21 Added french accent to skin
2023-08-24 fix some bug on VT100
2023-08-24 config was crashing the board!
2023-08-25 fix part of the language
2023-08-25 Change some txt to utf8 to ansi, because it was scrapping my french accent
2023-08-25 adding Stacktistic page to menu
2023-08-28 wip menu
2023-08-29 wip, menu input reading
2023-08-31 Some work on IP
2023-09-01 wip lwip
2023-09-05 Adding menu for SD Card diagnostic
2023-09-06 (wip) menu SD Card
2023-09-08 (wip) VT100 improvement
2023-09-11 lwip wip
2023-09-11 fix bad merge
2023-09-13 Adding user cli command file
2023-09-13 improve CLI
2023-09-13 fix merge
2023-09-14 improving Serial COMM
2023-09-19 wip GRBL clean-up
2023-09-20 Remove Timing setting for Widget... it won't be implemented
2023-09-21 Change a link in README.md
2023-09-21 update ignore list
2023-09-21 clean- error while trying to merge
2023-09-21 reinstalled missing files
2023-09-21 tried to enable debug
2023-09-21 adding LWIP debug
2023-09-22 Replace All '\r' with '\n' to sync log with LwIP.
2023-09-25 comment added
2023-09-26 Adding Random function lib using internal module
2023-09-27 testing Config/lwipopts.h
2023-09-28 added stat to memory pool
2023-10-03 CLI support Language (move from VT100)
2023-10-10 adding System Setting
2023-10-25 change label method, conditional callback call network
2023-10-27 wip language selection
2023-10-30 Language change in VT100 is working in both VT100 and in GUI
2023-10-31 adding option into misc menu
2023-11-03 wip Adding ADC
2023-11-23 WIP test for ChainList.. remove after successful test
2023-12-01 wip network + fix Lib_Stacktistic
2023-12-13 lwip in progress
2023-12-14 add mockup for MPU
2023-12-19 Added MPU Lib Support
2024-01-08 work on IP
2024-01-29 wip nanoIP
2024-02-13 It compile
2024-02-13 fix database
2024-02-22 wip sync digini
2024-02-27 remove stuff that goes into digini
2024-02-28 clean-up config
2024-03-04 fix uart now working like B4
2024-04-16 Added project Kicad
2024-04-17 kicad progress
2024-04-18 kicad
2024-04-19 wip kicad
2024-05-01 kicad wip
2024-05-14 wip Kicad.
2024-05-15 wip GRBL
2024-05-16 Adding MCP230xx driver and config
2024-05-17 move to DMA class
2024-05-17 Adding missing SPI4 to 6 in spi_var
2024-05-21 DMA wip
2024-05-29 wip backup
2024-05-30 WIP Relative PATH
2024-05-31 wip PATH
2024-06-03 Fix SPI
2024-06-04 config wip
2024-06-19 wip config
2024-06-20 fix config clock
2024-06-20 Fix GRBL, a lot of little change in Digini
2024-06-25 est done to fix VT100 and UART
2024-06-25 move comm
2024-06-26 updating digini.cfg
2024-06-26 sync Digini and update project
2024-06-27 adjust config and lib_comm integration
2024-07-12 WIP (not compiling)
2024-07-15 Sync project with Digini
2024-07-15 added missing generic VT100 menu item
2024-08-01 change config to sync with Digini
2024-09-11 fix config for new macro in CLI
2024-09-16 wip label
2024-09-16 wip database
2024-09-17 update config
2024-10-04 sync with Digini
2024-10-10 comment change
2024-10-11 sync digini
2024-10-22 SPI modification imply mod in config
2025-01-21 WIP config IO
2025-01-22 Wip IO
2025-10-02 sync app to Digini
2025-10-03 cleaning duty
2025-11-07 added missing dma_cfg.h
2025-11-07 updated Grafx driver
2025-11-10 move LCD clock config to clock init file
2025-11-16 add SDRAM config and modified IO
2025-11-17 sync BSP with Digini
2025-11-18 fix DMA in UART with the Config/uart_var.h
2025-11-19 improve clock config
2025-11-20 improve SVD file
2025-11-20 fix clock issue with uart
2026-03-28 move file for grafx
2026-03-30 wip grafx
2026-04-16 sync to new digini
2026-04-22 resync Digini
2026-04-24 sync new Digini
2026-05-11 sync grafx
2026-05-26 fix grafx
